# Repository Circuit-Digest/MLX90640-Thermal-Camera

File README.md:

# [MLX90640-Thermal-Camera](https://circuitdigest.com/microcontroller-projects/diy-thermal-camera-using-esp32-wrover-module-and-mlx90640-sensor) 

<br>

<div style="display: flex; flex-wrap: nowrap;">

</div>

<br>
<br>
<br>
<br>
<br>

<br>

Thermal Cameras are widely used in a wide range of industrial applications such as thermal performance monitoring, detecting temperature anomalies, thermal bench marking and many more. We even use thermal imaging even for defense and military applications. The most common application that we may come across, is might be the electronics repair industry. In repair industry the thermal cameras are a very important tool which can make the hardware debugging much easier especially where there are shorted parts are involved. The main concern regarding such thermal imager is that they are pretty expensive. 
So, in this project we are going to find some solution for that by making a DIY thermal imager using much cheaper available components. The cheaper thermal imaging sensors we have considered are the AMG8833 from Panasonic and MLX90640 and MLX90641 from Melexis. Even though the AMG8833 is the cheapest of them all it only has a resolution o f 8x8, while MLX90640 offers a resolution of 32x24 and MLX90641 offers a resolution of 16x12. Since the MLX90640 offers the best resolution in the price range we choose it for our DIY thermal camera.

<br>
[Note: As this projects are very simple we are only providing the code, schemaitic, and a few essential images if you want to get the images or code explanations do check out the Circuit Digest website.
<br>
<br>

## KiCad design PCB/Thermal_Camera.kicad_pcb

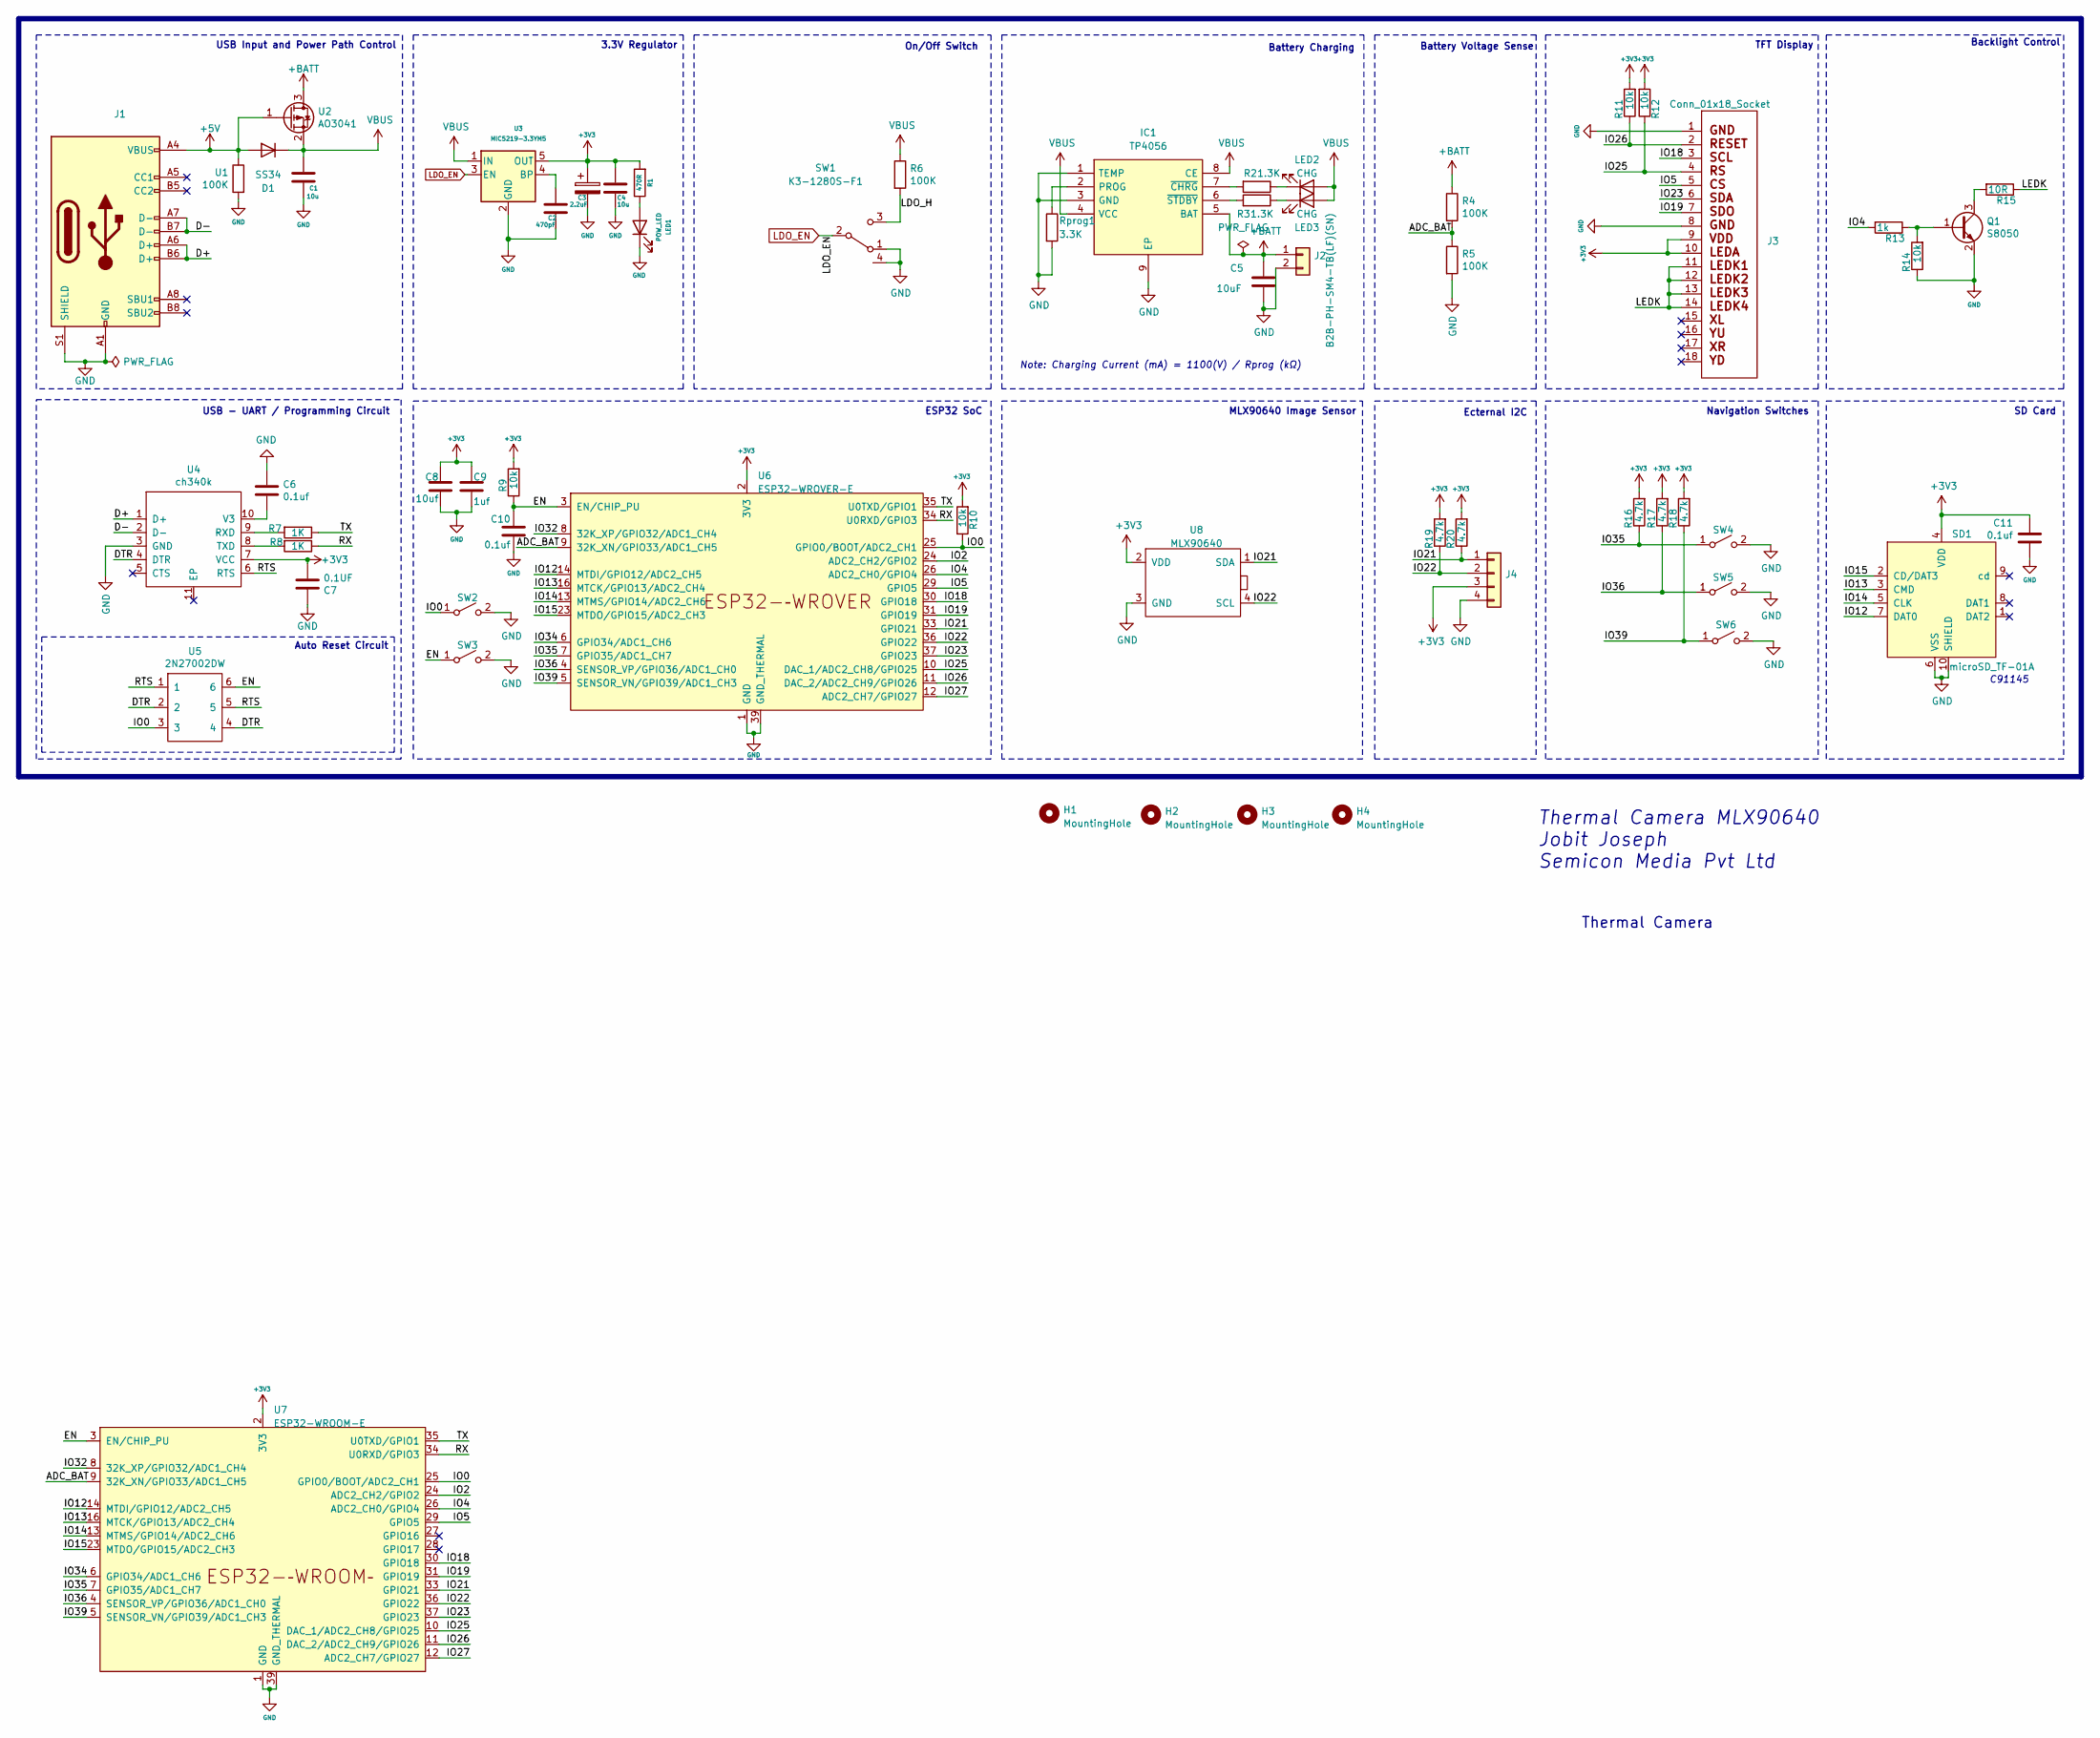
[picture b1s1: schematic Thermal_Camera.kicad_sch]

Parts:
C1, C4: 10u; C_0603_1608Metric
C2: 470pF; C_0603_1608Metric
C3: 2.2uF; C_0805_2012Metric
C5: 10uF; C_0603_1608Metric
C6, C10, C11: 0.1uf; C_0603_1608Metric
C7: 0.1UF; C_0603_1608Metric
C8: 10uf; C_0603_1608Metric
C9: 1uf; C_0603_1608Metric
D1: SS34; D_SMA
H1, H2, H3, H4: MountingHole; MountingHole_2.2mm_M2_ISO7380_Pad
IC1: TP4056; SOIC127P600X175-9N; Manufacturer_Part_Number TP4056-42-ESOP8
J1: USB_C_Receptacle_USB2.0; USB_C_Receptacle_HRO_TYPE-C-31-M-12
J2: B2B-PH-SM4-TB(LF)(SN); JST_PH_B2B-PH-SM4-TB_1x02-1MP_P2.00mm_Vertical
J3: Conn_01x18_Socket; 24LCDILI9341
J4: Stemma; JST_PH_B4B-PH-K_1x04_P2.00mm_Vertical
LED1: POW_LED; LED_0603_1608Metric
LED2, LED3: CHG; LED_0603_1608Metric
Q1: S8050; SOT-23
R1: 470R; R_0603_1608Metric
R2, R3: 1.3K; R_0603_1608Metric
R4, R5, R6: 100K; R_0603_1608Metric
R7, R8: 1K; R_0603_1608Metric
R9, R10, R11, R12, R14: 10k; R_0603_1608Metric
R13: 1k; R_0603_1608Metric
R15: 10R; R_0805_2012Metric
R16, R17, R18, R19, R20: 4.7k; R_0603_1608Metric
Rprog1: 3.3K; R_0603_1608Metric
SD1: microSD_TF-01A; microSD_TF-01A-C91145
SW1: K3-1280S-F1; slide switch spdt
SW2, SW3, SW4, SW5, SW6: TS-1088R-02526; Tactile 3x4x2mm TS-A010
U1: 100K; R_0603_1608Metric
U2: AO3041; SOT-23
U3: MIC5219-3.3YM5; SOT-23-5
U4: ch340k; ESSOP-10_3.9x4.9mm_P1.00mm
U5: 2N27002DW; SOT-363_SC-70-6
U6: ESP32-WROVER-E
U7: ESP32-WROOM-E; ESP32-WROOM-32E
U8: MLX90640

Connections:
+3V3: C3.1, C4.1, C7.2, C8.1, C9.1, C11.1, J3.9 (VDD), J3.10 (LEDA), J4.3, R1.2, R9.2, R10.2, R11.2, R12.2, R16.2, R17.2, R18.2, R19.2, R20.2, SD1.4 (VDD), U3.5 (OUT), U4.7 (VCC), U6.2 (3V3), U7.2 (3V3), U8.2 (VDD)
+5V: D1.2 (A), J1.A4 (VBUS), J1.A9 (VBUS), J1.B4 (VBUS), J1.B9 (VBUS), U1.1, U2.1 (G)
+BATT: C5.1, IC1.5 (BAT), J2.1, R4.1, U2.3 (D)
/ADC_BAT: R4.2, R5.1, U6.9 (32K_XN/GPIO33/ADC1_CH5), U7.9 (32K_XN/GPIO33/ADC1_CH5)
/D+: J1.A6 (D+), J1.B6 (D+), U4.1 (D+)
/D-: J1.A7 (D-), J1.B7 (D-), U4.2 (D-)
/DTR: U4.4 (DTR), U5.2, U5.4
/EN: C10.1, R9.1, SW3.1 (A), U5.6, U6.3 (EN/CHIP_PU), U7.3 (EN/CHIP_PU)
/IO2: U6.24 (ADC2_CH2/GPIO2), U7.24 (ADC2_CH2/GPIO2)
/IO4: R13.2, U6.26 (ADC2_CH0/GPIO4), U7.26 (ADC2_CH0/GPIO4)
/IO5: J3.5 (CS), U6.29 (GPIO5), U7.29 (GPIO5)
/IO12: SD1.7 (DAT0), U6.14 (MTDI/GPIO12/ADC2_CH5), U7.14 (MTDI/GPIO12/ADC2_CH5)
/IO13: SD1.3 (CMD), U6.16 (MTCK/GPIO13/ADC2_CH4), U7.16 (MTCK/GPIO13/ADC2_CH4)
/IO14: SD1.5 (CLK), U6.13 (MTMS/GPIO14/ADC2_CH6), U7.13 (MTMS/GPIO14/ADC2_CH6)
/IO15: SD1.2 (CD/DAT3), U6.23 (MTDO/GPIO15/ADC2_CH3), U7.23 (MTDO/GPIO15/ADC2_CH3)
/IO18: J3.3 (SCL), U6.30 (GPIO18), U7.30 (GPIO18)
/IO19: J3.7 (SDO), U6.31 (GPIO19), U7.31 (GPIO19)
/IO21: J4.1, R20.1, U6.33 (GPIO21), U7.33 (GPIO21), U8.1 (SDA)
/IO22: J4.2, R19.1, U6.36 (GPIO22), U7.36 (GPIO22), U8.4 (SCL)
/IO23: J3.6 (SDA), U6.37 (GPIO23), U7.37 (GPIO23)
/IO25: J3.4 (RS), R12.1, U6.10 (DAC_1/ADC2_CH8/GPIO25), U7.10 (DAC_1/ADC2_CH8/GPIO25)
/IO26: J3.2 (RESET), R11.1, U6.11 (DAC_2/ADC2_CH9/GPIO26), U7.11 (DAC_2/ADC2_CH9/GPIO26)
/IO27: U6.12 (ADC2_CH7/GPIO27), U7.12 (ADC2_CH7/GPIO27)
/IO32: U6.8 (32K_XP/GPIO32/ADC1_CH4), U7.8 (32K_XP/GPIO32/ADC1_CH4)
/IO34: U6.6 (GPIO34/ADC1_CH6), U7.6 (GPIO34/ADC1_CH6)
/IO36: R17.1, SW5.1 (A), U6.4 (SENSOR_VP/GPIO36/ADC1_CH0), U7.4 (SENSOR_VP/GPIO36/ADC1_CH0); also elsewhere on the board
/IO39: R18.1, SW6.1 (A), U6.5 (SENSOR_VN/GPIO39/ADC1_CH3), U7.5 (SENSOR_VN/GPIO39/ADC1_CH3); also elsewhere on the board
/LDO_H: R6.2, SW1.3 (C)
/LEDK: J3.11 (LEDK1), J3.12 (LEDK2), J3.13 (LEDK3), J3.14 (LEDK4), R15.1
/RTS: U4.6 (RTS), U5.1, U5.5
/RX: R8.1, U6.34 (U0RXD/GPIO3), U7.34 (U0RXD/GPIO3)
/TX: R7.1, U6.35 (U0TXD/GPIO1), U7.35 (U0TXD/GPIO1)
LDO_EN: SW1.2 (B), U3.3 (EN)
unnamed: IC1.2 (PROG), Rprog1.1
unnamed: IC1.7 (~CHRG), R2.2
unnamed: IC1.6 (~STDBY), R3.2
unnamed: LED1.2 (A), R1.1
unnamed: LED2.1 (K), R2.1
unnamed: LED3.1 (K), R3.1
unnamed: Q1.3 (C), R15.2
unnamed: Q1.1 (E), R13.1, R14.2
unnamed: C2.1, U3.4 (BP)
unnamed: R7.2, U4.9 (RXD)
unnamed: R8.2, U4.8 (TXD)
unnamed: C6.2, U4.10 (V3)
VBUS: C1.1, D1.1 (K), IC1.4 (VCC), IC1.8 (CE), LED2.2 (A), LED3.2 (A), R6.1, U2.2 (S), U3.1 (IN)

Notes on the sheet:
Auto Reset Circuit
Battery Charging
Navigation Switches
Thermal Camera MLX90640 Jobit Joseph Semicon Media Pvt Ltd
TFT Display
MLX90640 Image Sensor
On/Off Switch
Ecternal I2C
Note: Charging Current (mA) = 1100(V) / Rprog (kΩ)
ESP32 SoC
C91145
Backlight Control
SD Card
3.3V Regulator
Battery Voltage Sense
USB Input and Power Path Control
Thermal Camera
USB - UART / Programming Circuit

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
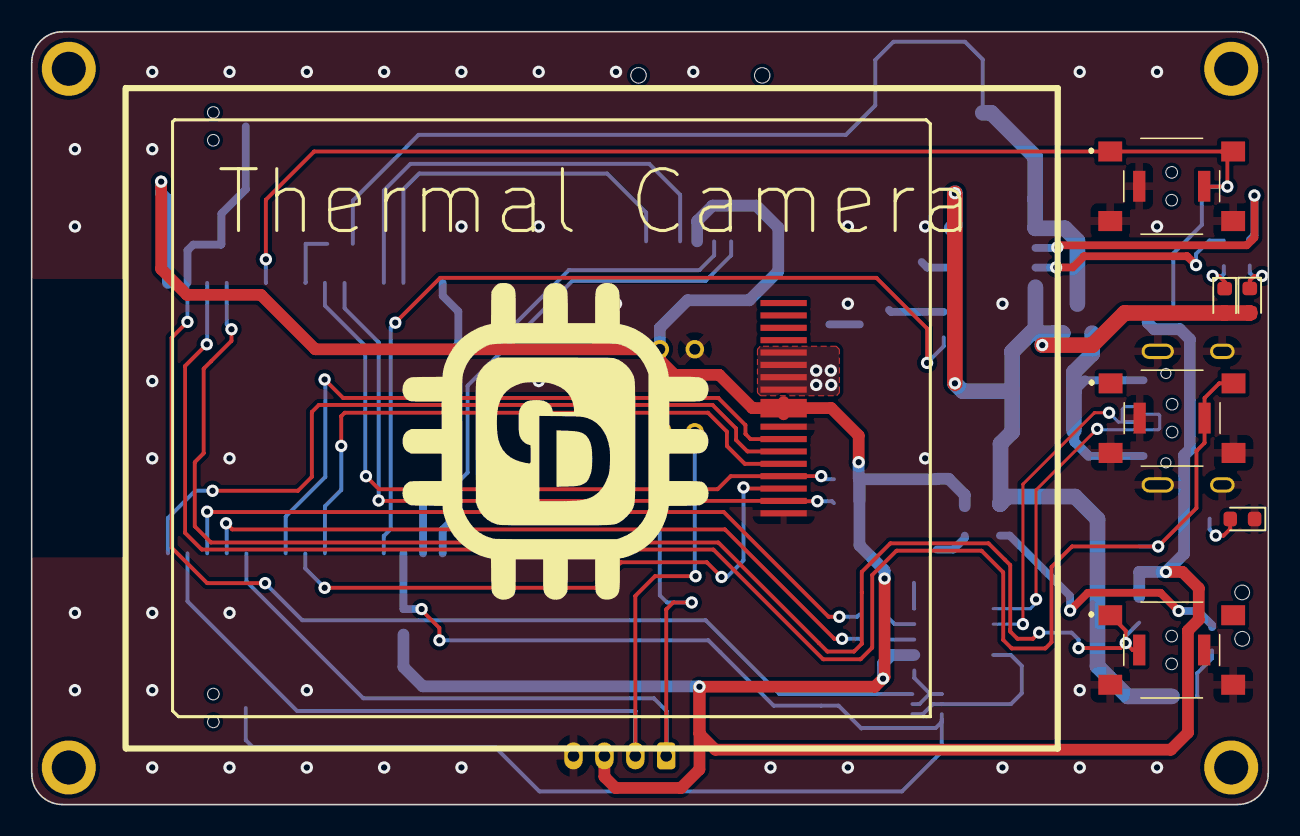
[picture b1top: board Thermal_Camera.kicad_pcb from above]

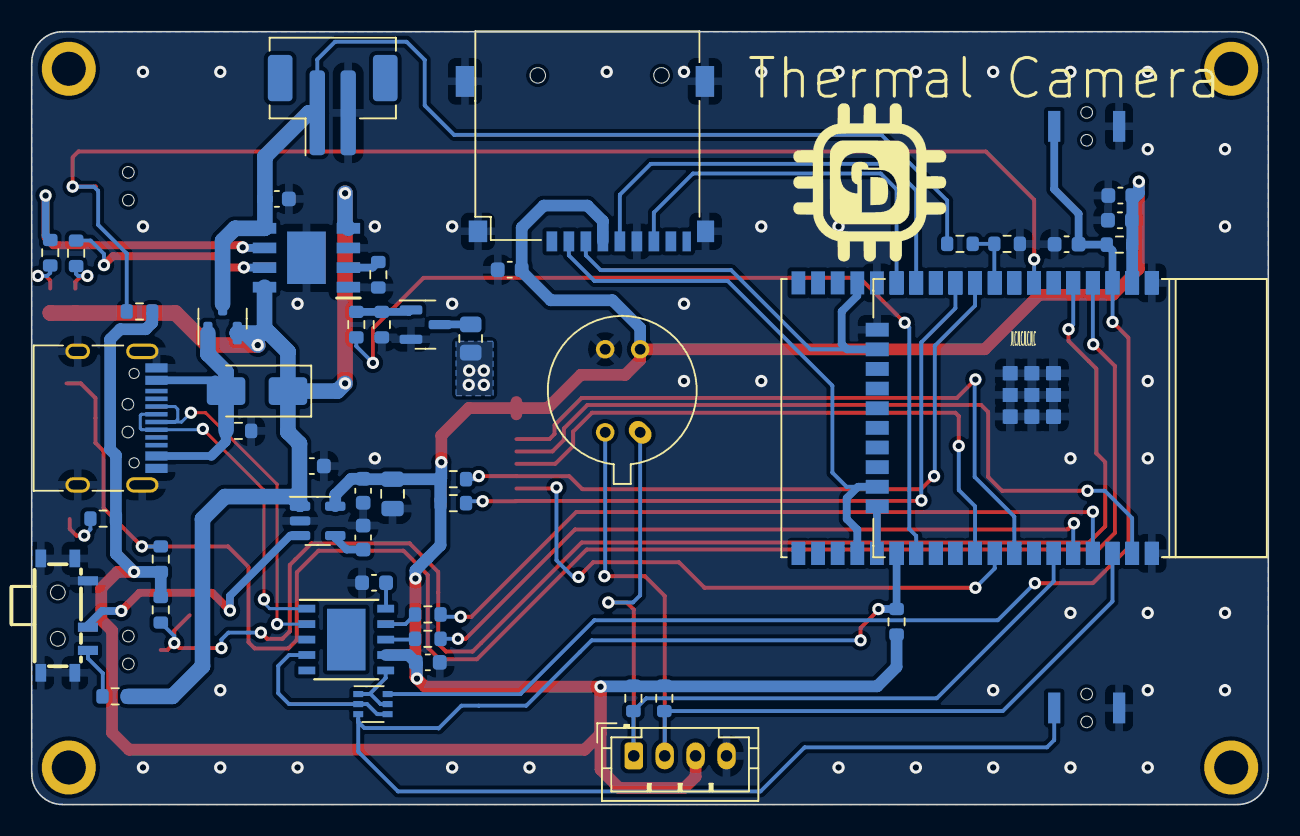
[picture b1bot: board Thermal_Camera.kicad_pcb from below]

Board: 2 copper layers, 80.0 x 50.0 mm, 64 parts (50 on the bottom side), 49 nets.

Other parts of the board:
SW2#2, SW2#3: SW_SPST; PTS645SL43SMTR92LFS
SW2#4: TS-1088R-02526; Tactile 3x4x2mm TS-A010

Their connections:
/IO36: SW2#2.2 (A); also elsewhere on the board
/IO39: SW2#3.1 (A); also elsewhere on the board

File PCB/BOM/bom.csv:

Designator,Footprint,Quantity,Value,LCSC Part #
"C1, C4",603,2,10u,
"C10, C11, C6, C7",603,4,0.1uf,
C2,603,1,470pF,
C3,805,1,2.2uF,
"C5, C8",603,2,10uF,
C9,603,1,1uf,
D1,D_SMA,1,SS34,
"H1, H2, H3, H4",MountingHole_2.2mm_M2_ISO7380_Pad,4,MountingHole,
IC1,SOIC127P600X175-9N,1,TP4056,
J1,USB_C_Receptacle_HRO_TYPE-C-31-M-12,1,USB_C_Receptacle_USB2.0,
J2,JST_PH_B2B-PH-SM4-TB_1x02-1MP_P2.00mm_Vertical,1, B2B-PH-SM4-TB(LF)(SN) ,
J3,24LCDILI9341,1,Conn_01x18_Socket,
J4,JST_PH_B4B-PH-K_1x04_P2.00mm_Vertical,1,Stemma,
LED1,603,1,POW_LED,
"LED2, LED3",603,2,CHG,
Q1,SOT-23,1,S8050,
R1,603,1,470R,
"R10, R11, R12, R14, R9",603,5,10k,
"R13, R7, R8",603,3,1k,
R15,805,1,10R,
"R16, R17, R18, R19, R20",603,5,4.7k,
"R2, R3",603,2,1.3K,
"R4, R5, R6, U1",603,4,100K,
Rprog1,603,1,3.3K,
SD1,microSD_TF-01A-C91145,1,microSD_TF-01A,
SW1,slide switch spdt,1,K3-1280S-F1 ,
"SW2_4, SW2_3, SW2_2",PTS645SL43SMTR92LFS,3,SW_SPST,
"SW2, SW3, SW4, SW5, SW6",Tactile 3x4x2mm TS-A010,5,TS-1088R-02526 ,
U2,SOT-23,1,AO3401,
U3,SOT-23-5,1,MIC5219-3.3YM5,
U4,ESSOP-10_3.9x4.9mm_P1.00mm,1,ch340k,
U5,SOT-363_SC-70-6,1,2N7002DW,
U6,ESP32-WROVER-E,1,ESP32-WROVER-E,
U7,ESP32-WROOM-32E,1,ESP32-WROOM-E,
U8,MLX90640,1,MLX90640,

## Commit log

2023-09-04 Create t
